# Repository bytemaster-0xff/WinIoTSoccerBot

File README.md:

# WinIoT SoccerBot has moved!
## [New Home](https://github.com/TampaIoT/TankBot)

This repository will no longer be maintained

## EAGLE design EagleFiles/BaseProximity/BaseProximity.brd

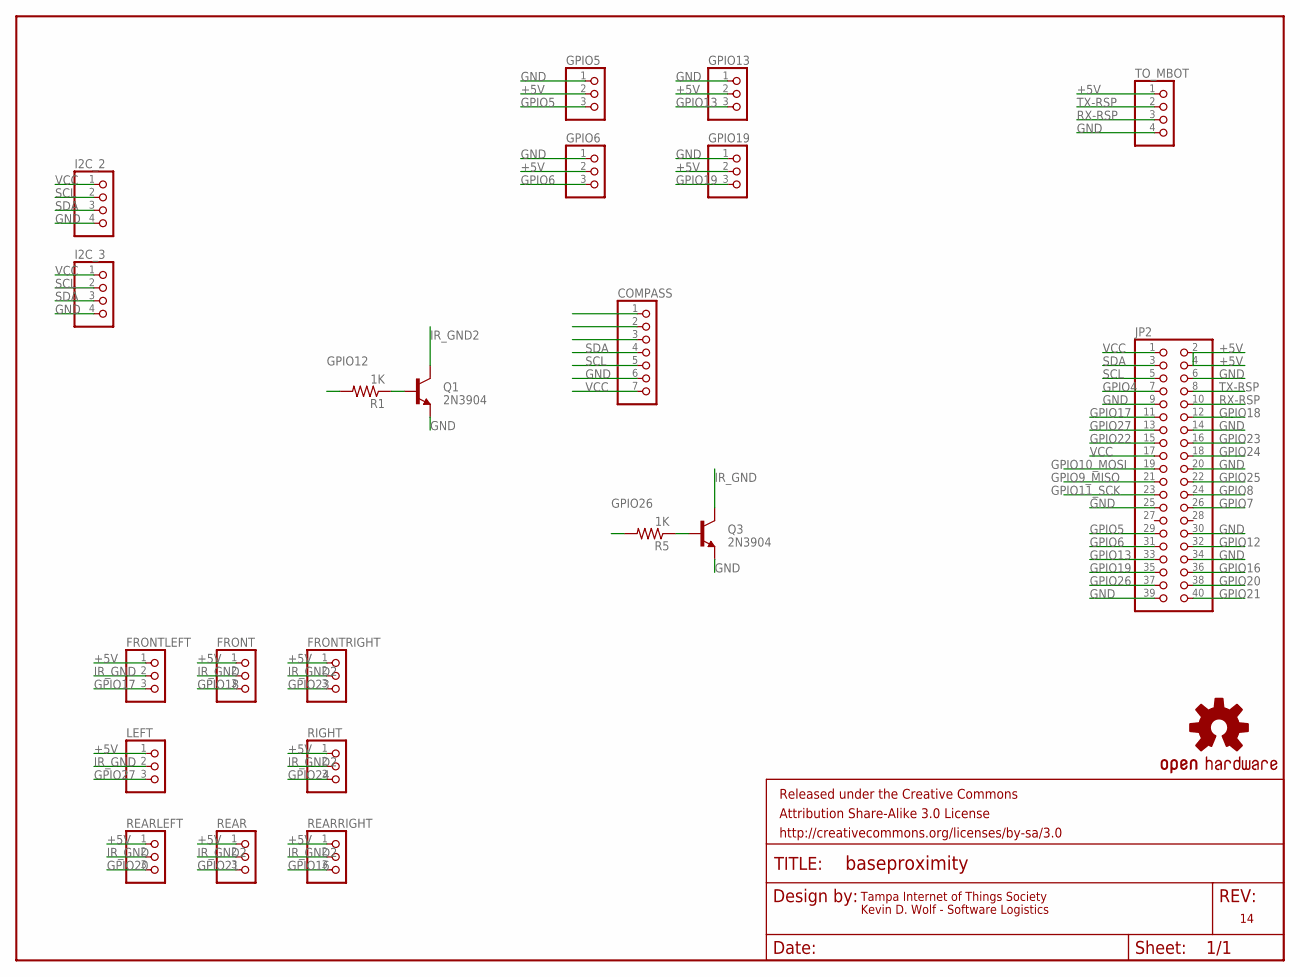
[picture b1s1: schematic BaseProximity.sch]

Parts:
COMPASS: PINHD-1X7; 1X07
FRAME1: FRAME-LETTER; CREATIVE_COMMONS
FRONT: PINHD-1X3; 1X03
FRONTLEFT: PINHD-1X3; 1X03
FRONTRIGHT: PINHD-1X3; 1X03
GPIO5, GPIO6, GPIO13, GPIO19: PINHD-1X3; 1X03
I2C_2, I2C_3: PINHD-1X4; 1X04
JP2: PINHD-2X20; 2X20
LEFT: PINHD-1X3; 1X03
Q1, Q3: 2N3904; TO-92-EZ
R1, R5: 1K; AXIAL-0.3EZ
REAR: PINHD-1X3; 1X03
REARLEFT: PINHD-1X3; 1X03
REARRIGHT: PINHD-1X3; 1X03
RIGHT: PINHD-1X3; 1X03
TO_MBOT: PINHD-1X4; 1X04
U$3: OSHW-LOGOS; OSHW-LOGO-S

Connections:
+5V: FRONT.1, FRONTLEFT.1, FRONTRIGHT.1, GPIO5.2, GPIO6.2, GPIO13.2, GPIO19.2, JP2.2, JP2.4, LEFT.1, REAR.1, REARLEFT.1, REARRIGHT.1, RIGHT.1, TO_MBOT.1
GND: COMPASS.6, GPIO5.1, GPIO6.1, GPIO13.1, GPIO19.1, I2C_2.4, I2C_3.4, JP2.6, JP2.9, JP2.14, JP2.20, JP2.25, JP2.30, JP2.34, JP2.39, Q1.1 (E), Q3.1 (E), TO_MBOT.4
GPIO4: JP2.7
GPIO5: GPIO5.3, JP2.29
GPIO6: GPIO6.3, JP2.31
GPIO7: JP2.26
GPIO8: JP2.24
GPIO9_MISO: JP2.21
GPIO10_MOSI: JP2.19
GPIO11_SCK: JP2.23
GPIO12: JP2.32, R1.P$2 (2)
GPIO13: GPIO13.3, JP2.33
GPIO16: JP2.36, REARRIGHT.3
GPIO17: FRONTLEFT.3, JP2.11
GPIO18: FRONT.3, JP2.12
GPIO19: GPIO19.3, JP2.35
GPIO20: JP2.38, REARLEFT.3
GPIO21: JP2.40, REAR.3
GPIO22: JP2.15
GPIO23: FRONTRIGHT.3, JP2.16
GPIO24: JP2.18, RIGHT.3
GPIO25: JP2.22
GPIO26: JP2.37, R5.P$2 (2)
GPIO27: JP2.13, LEFT.3
IR_GND: FRONT.2, FRONTLEFT.2, LEFT.2, Q3.3 (C), REARLEFT.2
IR_GND2: FRONTRIGHT.2, Q1.3 (C), REAR.2, REARRIGHT.2, RIGHT.2
unnamed: Q1.2 (B), R1.P$1 (1)
unnamed: Q3.2 (B), R5.P$1 (1)
RX-RSP: JP2.10, TO_MBOT.3
SCL: COMPASS.5, I2C_2.2, I2C_3.2, JP2.5
SDA: COMPASS.4, I2C_2.3, I2C_3.3, JP2.3
TX-RSP: JP2.8, TO_MBOT.2
VCC: COMPASS.7, I2C_2.1, I2C_3.1, JP2.1, JP2.17

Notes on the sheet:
Tampa Internet of Things Society
Kevin D. Wolf - Software Logistics

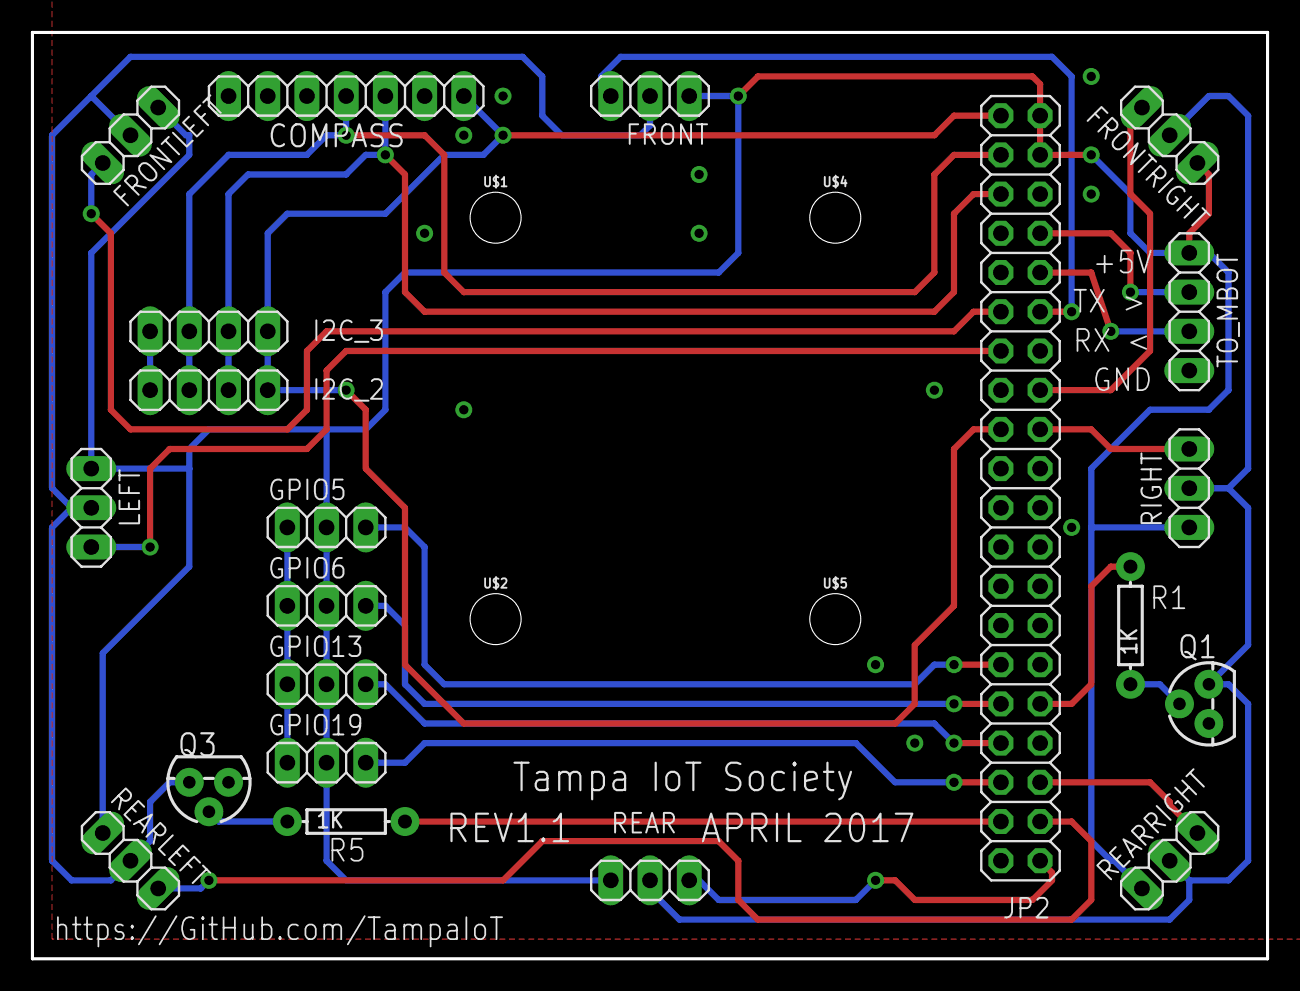
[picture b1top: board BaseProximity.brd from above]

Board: 2 copper layers, 80.0 x 60.0 mm, 27 parts (1 on the bottom side), 25 nets.

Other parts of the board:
U$1, U$2, U$4, U$5: STAND-OFF

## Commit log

2016-12-01 created initial project structure
2016-12-01 initial app, connects to bluetooth, doesn't stream data.
2016-12-01 Added PPTX
2016-12-01 updated readme file
2016-12-05 remove bin file, add initial mblox protocol
2016-12-06 send/receive mBot via blueooth
2016-12-14 added icons, working protocol
2016-12-15 Modified ther UI Slightly. No code changes
2016-12-20 refactor for re-usable classes
2016-12-20 added basic functionality for HID integration
2016-12-22 can now control movement via app
2016-12-23 added refresh timer
2016-12-26 added speed control and basic front obsticle avoidance
2016-12-27 Fleshed out program from Kevin
2016-12-27 Revert "Fleshed out program from Kevin"
    This reverts commit 6c70a9e94389fe97a5f7e314c725a839fcd3fd9f.
2016-12-29 add starting point for custom firmware
2017-01-02 Update MainPage.xaml
    Icons for movement buttons.
2017-01-05 extended protocol
2017-01-05 protocol working for setting mode and sending motor control in one command
2017-01-05 add support for LED matrix and bar for sonar
2017-01-05 fix original firmware issues
2017-01-05 change isAdavancedAPI
2017-01-06 Update MainPage.xaml
    Display full Device Id.
2017-01-07 added schematic for proximity pi tin
2017-01-07 v1 of proximity board completed
2017-01-30 Add initial instructions for based PC setup and using firmata firmware
2017-01-30 add shopping list and getting started
2017-01-30 add links to readme
2017-02-08 very broken refactor branch
2017-02-08 add image files
2017-02-09 web server and api server online
2017-02-09 start wiring stuff together
2017-02-09 added tcpip channel and watcher
2017-02-09 get name from computer
2017-02-09 serial port now talking to mBot from Pi
2017-02-09 version for 2/9/2017 meeting, mostly working very little testing
2017-02-09 update documents
2017-02-09 update dox
2017-02-10 update broken image
2017-02-10 fix typo in wiring
2017-02-10 update parts lists with different stand offs
2017-02-12 Add first pass of docs for the Windows Desktop App
2017-02-12 add gcode for soccerbot adapter
2017-03-06 updated dox, and stubs for controlling with XBox Controller
2017-03-06 added another option for powersupply
2017-03-08 start work on sockets commot
2017-03-08 project/solution updates
2017-03-08 SSDP Discovery Fixed
2017-03-08 message parser working
2017-03-08 play sound when connect to mBot
2017-03-08 can connect from UWP app to mBot
2017-03-08 generate pin
2017-03-08 pinging now online
2017-03-09 playing tone on connect/disconnect and show lights
2017-03-09 add ui for device client, add message types added view model and sensors
2017-03-09 updates for march meeting
2017-03-09 add link for march meeting
2017-03-10 Remove link to unusable XBox controller
    This is the one I bought that was evidently _not_ for an XBox. There is no way to connect this to a PC over USB.
2017-03-14 board design w/ switch IR
2017-03-20 board order for v1.0
2017-03-28 added solder stations
2017-03-28 updated april plan
2017-04-04 add early sensor board support and pictures for creating board
2017-04-04 add pix for compass
2017-04-05 added additional instructions for building sensor board
2017-04-05 update pictures
2017-04-05 add cam files for ranger/rover cutout
2017-04-05 sending sensors from device to UWP app (not happy with code structure at this point)
2017-04-06 update instructions for board
2017-04-06 fix pix links in sensor board file
2017-04-06 add warning about main rasberry pi connector
2017-04-07 update project for VS2015 support
2017-04-25 updated board for new order
2017-06-08 Create README.md
    moved repo

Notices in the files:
parts and their libraries:
SparkFun-Aesthetics: Licensing: CC v3.0 Share-Alike You are welcome to use this library for commercial purposes.
SparkFun-Aesthetics: Released under the Creative Commons Attribution Share-Alike 3.0 License
SparkFun-Aesthetics: http://creativecommons.org/licenses/by-sa/3.0
